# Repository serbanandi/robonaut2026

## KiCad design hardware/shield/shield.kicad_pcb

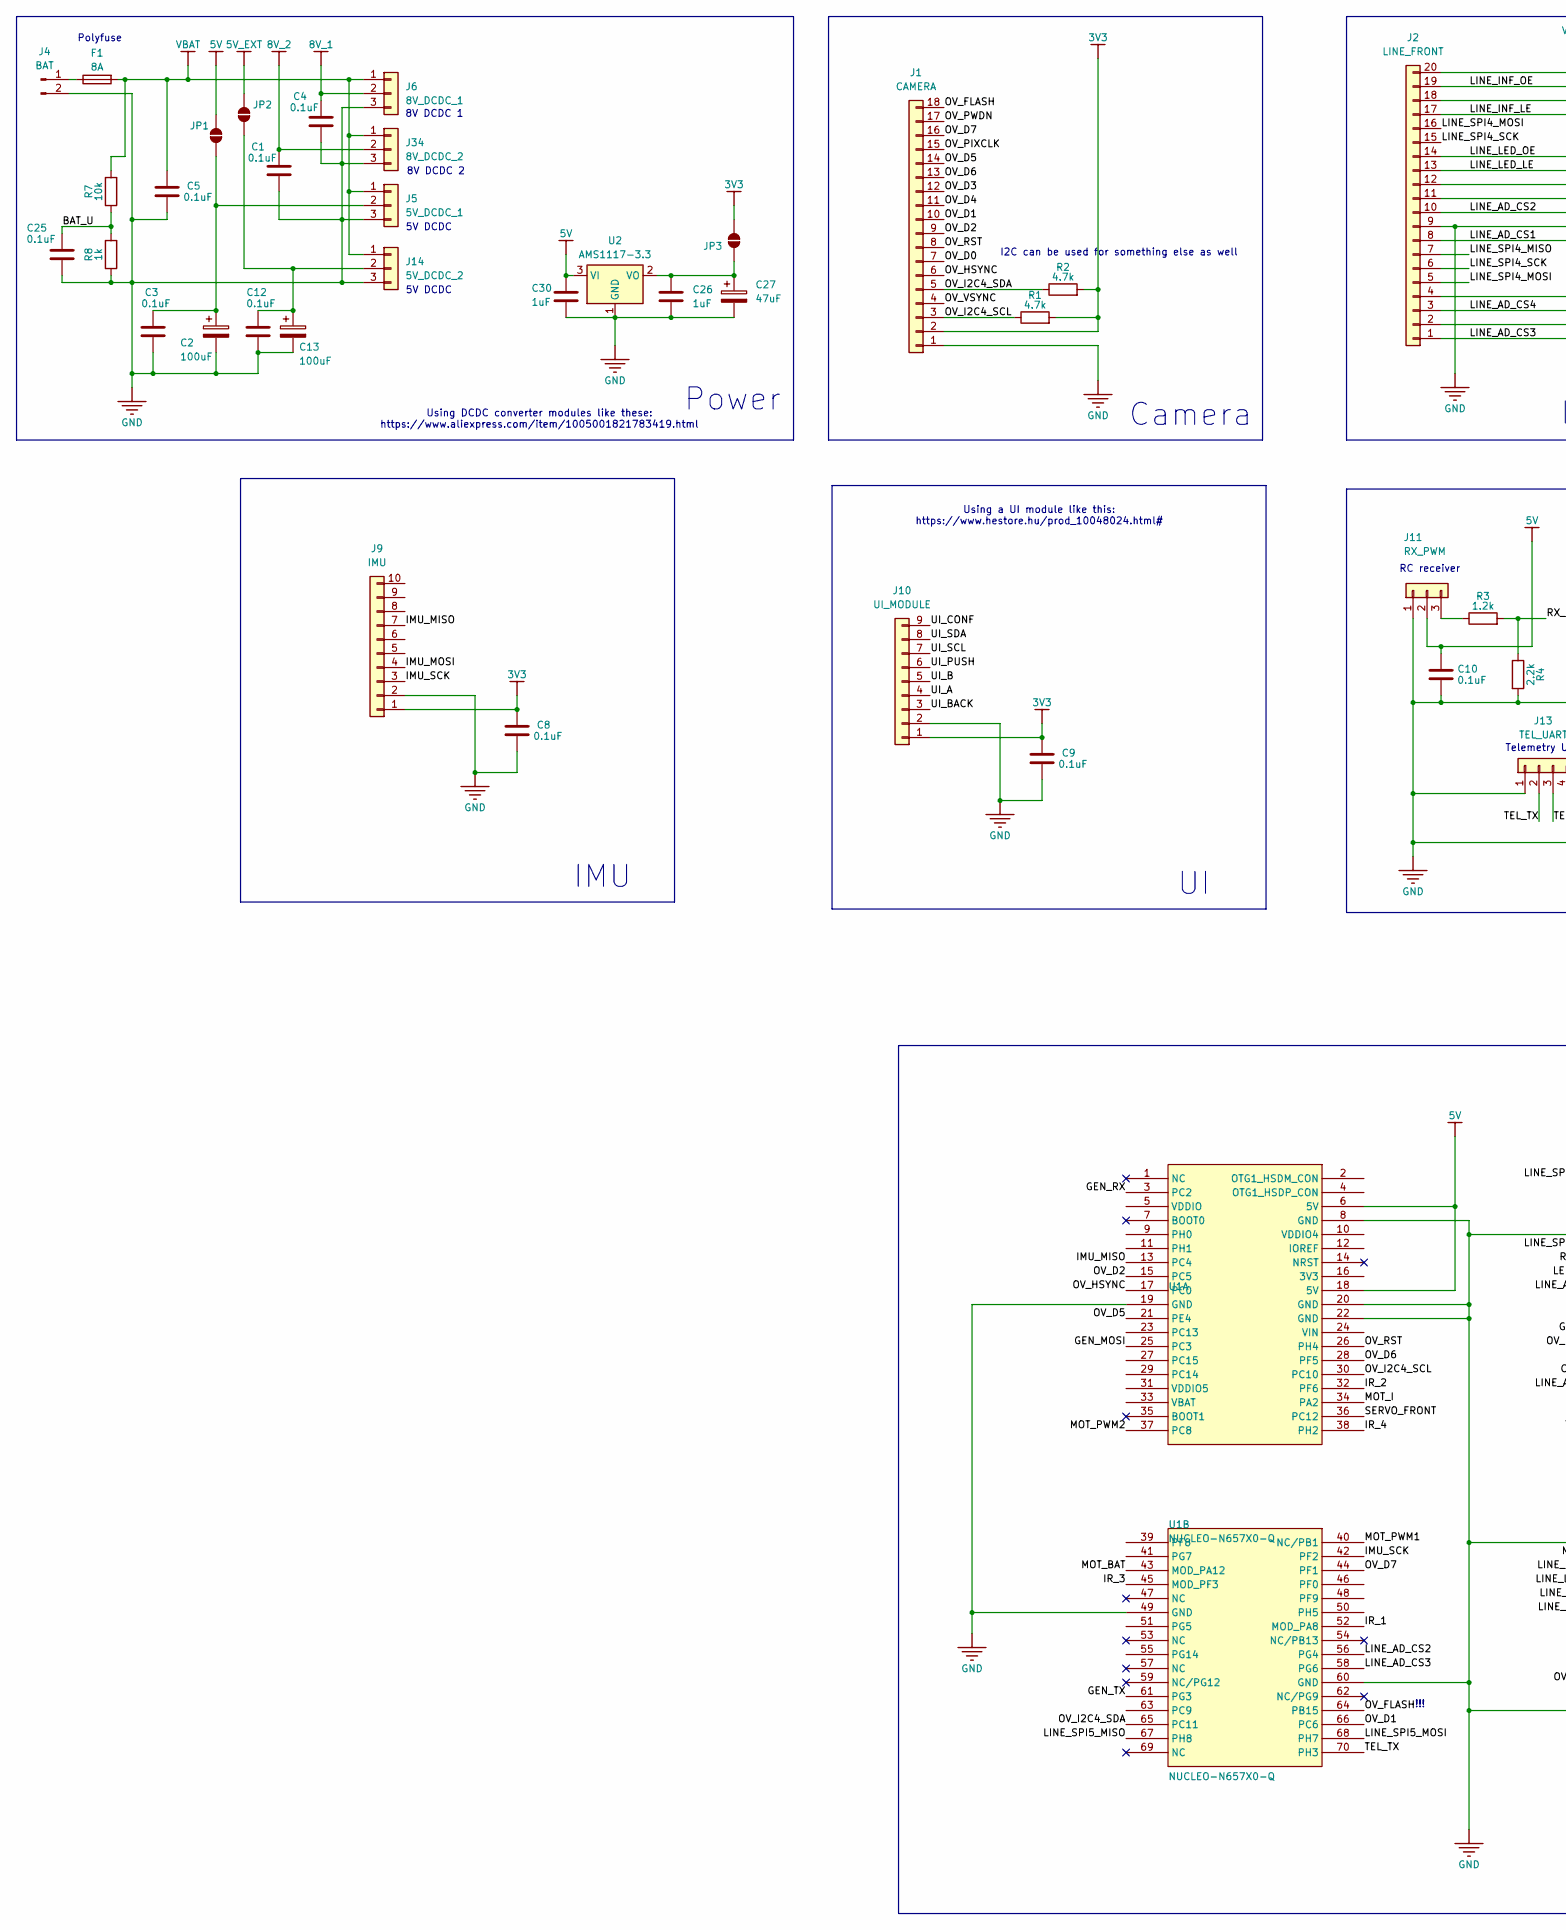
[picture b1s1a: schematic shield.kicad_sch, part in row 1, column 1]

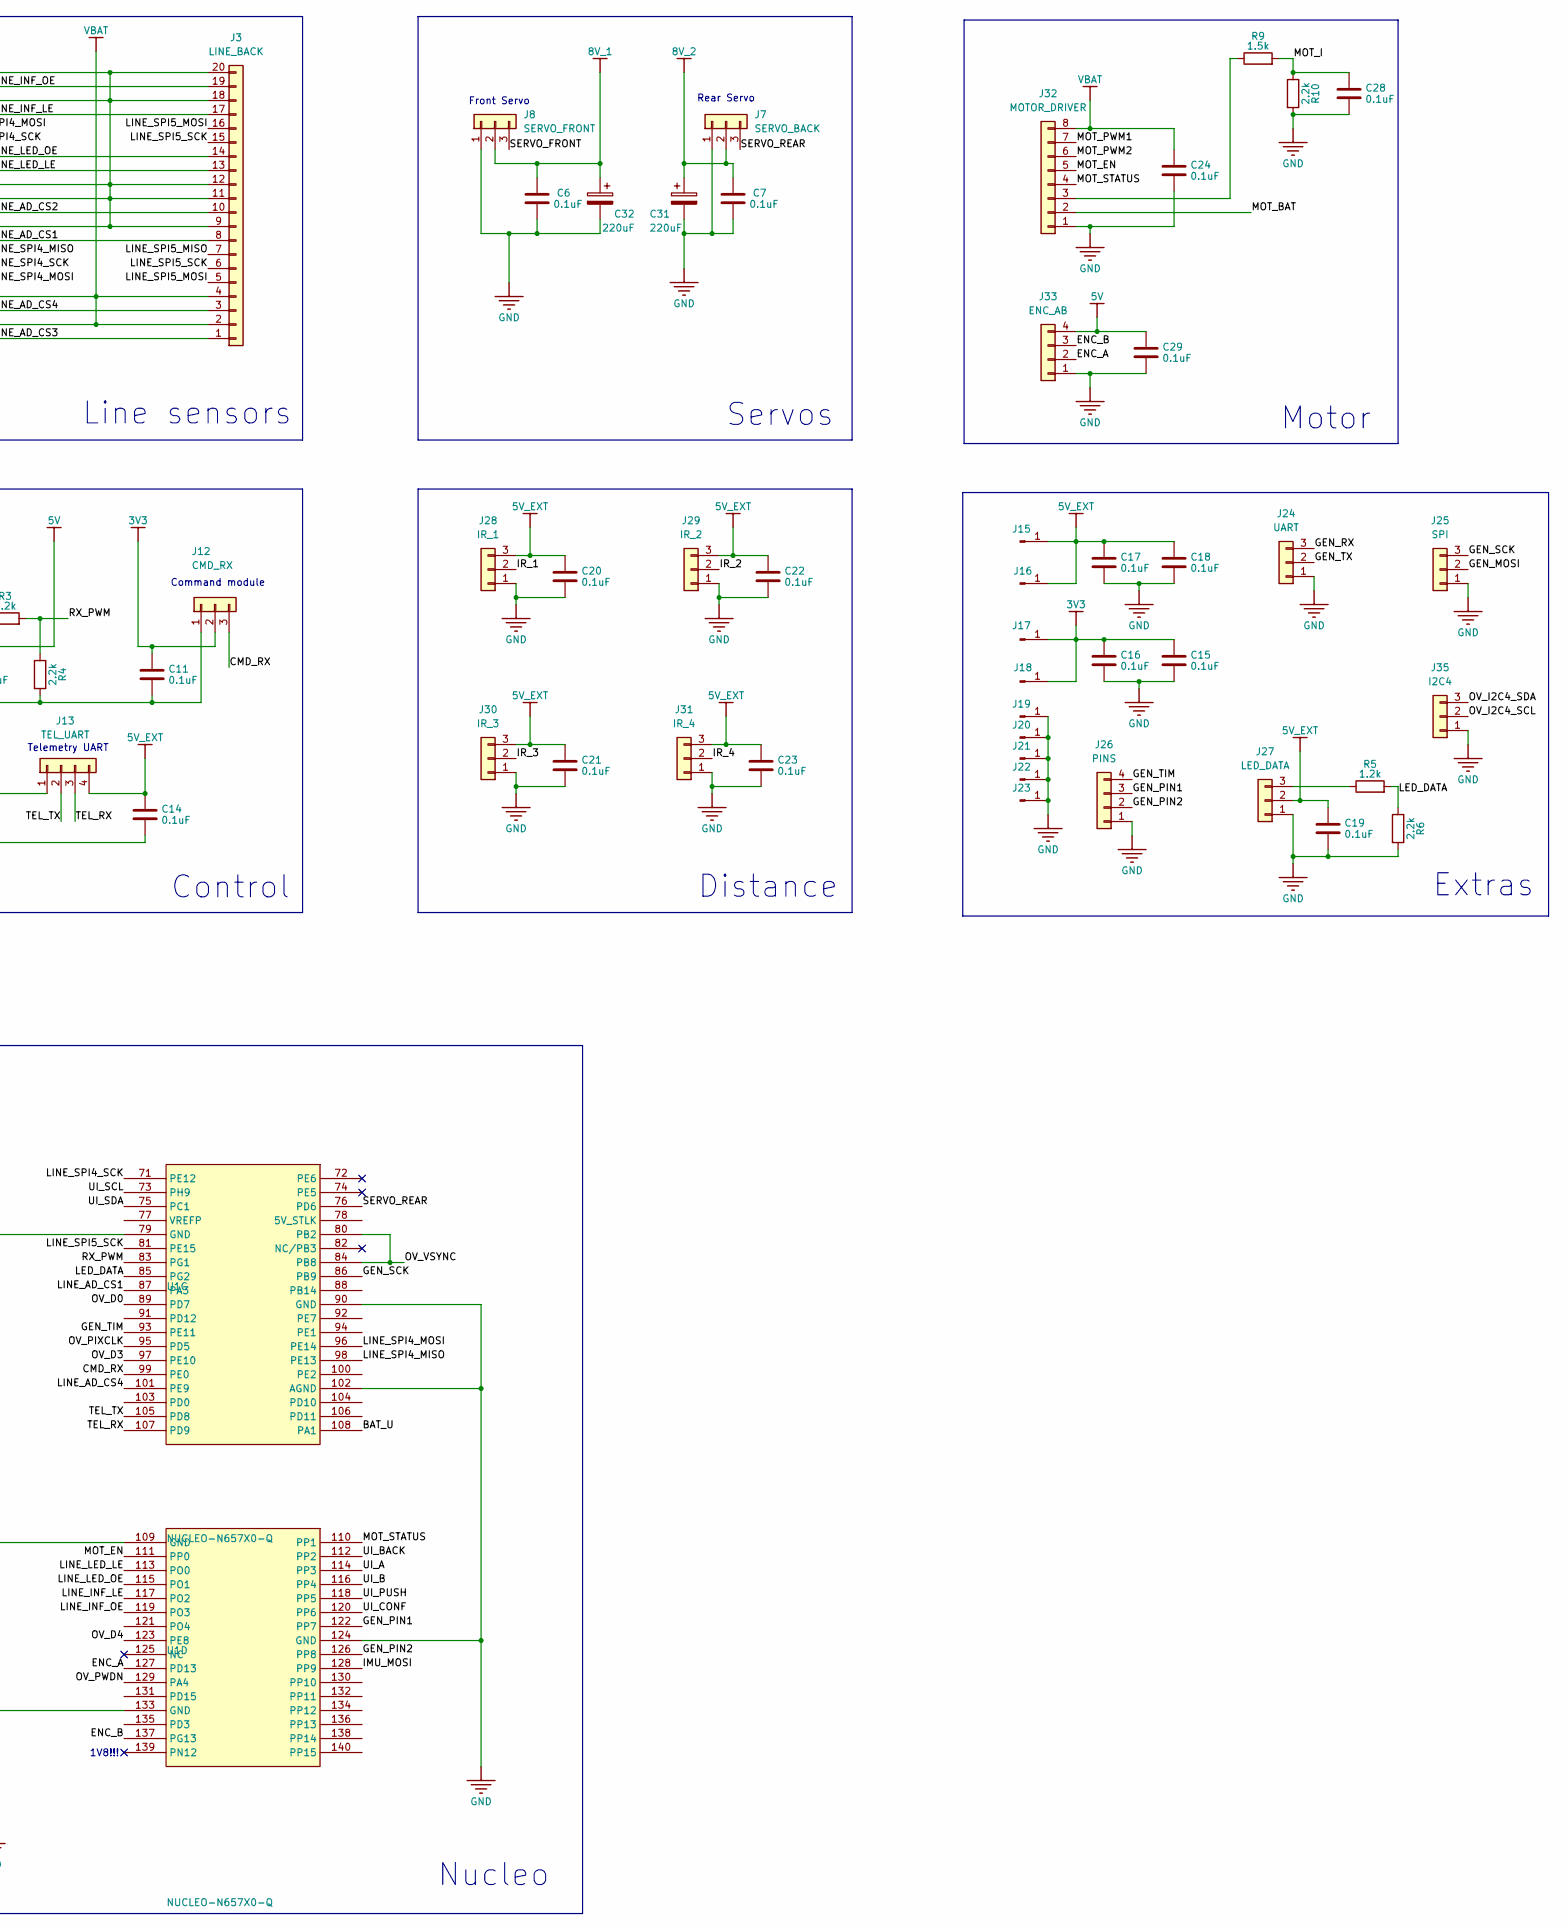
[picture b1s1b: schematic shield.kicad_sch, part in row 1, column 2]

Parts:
C1, C3, C4, C5, C6, C7, C8, C9, C10, C11, C12, C14, C15, C16, C17, C18, C19, C20, C21, C22, C23, C24, C25, C28, C29: 0.1uF; C_0603_1608Metric
C2, C13: 100uF; CP_Elec_5x5.8
C26, C30: 1uF; C_0805_2012Metric
C27: 47uF; CP_Elec_5x5.3
C31, C32: 220uF; CP_Elec_6.3x7.7
F1: 8A; Fuseholder_Blade_Mini_Keystone_3568
J1: CAMERA; PinHeader_2x09_P2.54mm_Horizontal
J2: LINE_FRONT; PinHeader_2x10_P2.54mm_Horizontal
J3: LINE_BACK; PinHeader_2x10_P2.54mm_Horizontal
J4: BAT; TerminalBlock_MaiXu_MX126-5.0-02P_1x02_P5.00mm
J5: 5V_DCDC_1; PinHeader_1x03_P2.54mm_Vertical
J6: 8V_DCDC_1; PinHeader_1x03_P2.54mm_Vertical
J7: SERVO_BACK; PinHeader_1x03_P2.54mm_Horizontal
J8: SERVO_FRONT; PinHeader_1x03_P2.54mm_Horizontal
J9: IMU; PinHeader_1x10_P2.54mm_Vertical
J10: UI_MODULE; JST_SH_SM09B-SRSS-TB_1x09-1MP_P1.00mm_Horizontal
J11: RX_PWM; JST_SH_SM03B-SRSS-TB_1x03-1MP_P1.00mm_Horizontal
J12: CMD_RX; JST_SH_SM03B-SRSS-TB_1x03-1MP_P1.00mm_Horizontal
J13: TEL_UART; JST_SH_SM04B-SRSS-TB_1x04-1MP_P1.00mm_Horizontal
J14: 5V_DCDC_2; PinHeader_1x03_P2.54mm_Vertical
J15: 5V_TP1; Pin_D0.7mm_L6.5mm_W1.8mm_FlatFork
J16: 5V_TP2; Pin_D0.7mm_L6.5mm_W1.8mm_FlatFork
J17: 3V3_TP3; Pin_D0.7mm_L6.5mm_W1.8mm_FlatFork
J18: 3V3_TP4; Pin_D0.7mm_L6.5mm_W1.8mm_FlatFork
J19: GND_TP1; Pin_D0.7mm_L6.5mm_W1.8mm_FlatFork
J20: GND_TP2; Pin_D0.7mm_L6.5mm_W1.8mm_FlatFork
J21: GND_TP3; Pin_D0.7mm_L6.5mm_W1.8mm_FlatFork
J22: GND_TP4; Pin_D0.7mm_L6.5mm_W1.8mm_FlatFork
J23: GND; Pin_D0.7mm_L6.5mm_W1.8mm_FlatFork
J24: UART; PinHeader_1x03_P1.00mm_Vertical
J25: SPI; PinHeader_1x03_P1.00mm_Vertical
J26: PINS; PinHeader_1x04_P1.00mm_Vertical
J27: LED_DATA; JST_SH_SM03B-SRSS-TB_1x03-1MP_P1.00mm_Horizontal
J28: IR_1; JST_SH_SM03B-SRSS-TB_1x03-1MP_P1.00mm_Horizontal
J29: IR_2; JST_SH_SM03B-SRSS-TB_1x03-1MP_P1.00mm_Horizontal
J30: IR_3; JST_SH_SM03B-SRSS-TB_1x03-1MP_P1.00mm_Horizontal
J31: IR_4; JST_SH_SM03B-SRSS-TB_1x03-1MP_P1.00mm_Horizontal
J32: MOTOR_DRIVER; JST_SH_SM08B-SRSS-TB_1x08-1MP_P1.00mm_Horizontal
J33: ENC_AB; JST_SH_SM04B-SRSS-TB_1x04-1MP_P1.00mm_Horizontal
J34: 8V_DCDC_2; PinHeader_1x03_P2.54mm_Vertical
J35: I2C4; PinHeader_1x03_P1.00mm_Vertical
JP1: 5V_1; SolderJumper-2_P1.3mm_Open_TrianglePad1.0x1.5mm
JP2: 5V_2; SolderJumper-2_P1.3mm_Open_TrianglePad1.0x1.5mm
JP3: 3V3; SolderJumper-2_P1.3mm_Open_TrianglePad1.0x1.5mm
R1, R2: 4.7k; R_0603_1608Metric
R3, R5: 1.2k; R_0603_1608Metric
R4, R6, R10: 2.2k; R_0603_1608Metric
R7: 10k; R_0603_1608Metric
R8: 1k; R_0603_1608Metric
R9: 1.5k; R_0603_1608Metric
U1: NUCLEO-N657X0-Q; FP_NUCLEO-144 - N6
U2: AMS1117-3.3; SOT-223-3_TabPin2

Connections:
3V3: C8.1, C9.1, C11.1, C15.1, C16.1, J1.2, J9.1, J10.1, J12.2, J17.1, J18.1, JP3.1 (A), R1.2, R2.2
5V: C10.1, C29.1, C30.1, J11.2, J33.4, JP1.2 (B), U1.6 (5V), U1.18 (5V), U2.3 (VI)
5V_EXT: C14.1, C17.1, C18.1, C19.1, C20.1, C21.1, C22.1, C23.1, J13.4, J15.1, J16.1, J27.2, J28.3, J29.3, J30.3, J31.3, JP2.2 (B)
8V_1: C4.1, C6.1, C32.1, J6.2, J8.2
8V_2: C1.1, C7.1, C31.1, J7.2, J34.2
/BAT_U: C25.1, R7.1, R8.2, U1.108 (PA1)
/CMD_RX: J12.3, U1.99 (PE0)
/ENC_A: J33.2, U1.127 (PD13)
/ENC_B: J33.3, U1.137 (PG13)
/GEN_MOSI: J25.2, U1.25 (PC3)
/GEN_PIN1: J26.3, U1.122 (PP7)
/GEN_PIN2: J26.2, U1.126 (PP8)
/GEN_RX: J24.3, U1.3 (PC2)
/GEN_SCK: J25.3, U1.86 (PB9)
/GEN_TIM: J26.4, U1.93 (PE11)
/GEN_TX: J24.2, U1.61 (PG3)
/IMU_MISO: J9.7, U1.13 (PC4)
/IMU_MOSI: J9.4, U1.128 (PP9)
/IMU_SCK: J9.3, U1.42 (PF2)
/IR_1: J28.2, U1.52 (MOD_PA8)
/IR_2: J29.2, U1.32 (PF6)
/IR_3: J30.2, U1.45 (MOD_PF3)
/IR_4: J31.2, U1.38 (PH2)
/LED_DATA: R5.2, R6.1, U1.85 (PG2)
/LINE_AD_CS1: J2.8, J3.8, U1.87 (PA3)
/LINE_AD_CS2: J2.10, J3.10, U1.56 (PG4)
/LINE_AD_CS3: J2.1, J3.1, U1.58 (PG6)
/LINE_AD_CS4: J2.3, J3.3, U1.101 (PE9)
/LINE_INF_LE: J2.17, J3.17, U1.117 (PO2)
/LINE_INF_OE: J2.19, J3.19, U1.119 (PO3)
/LINE_LED_LE: J2.13, J3.13, U1.113 (PO0)
/LINE_LED_OE: J2.14, J3.14, U1.115 (PO1)
/LINE_SPI4_MISO: J2.7, U1.98 (PE13)
/LINE_SPI4_MOSI: J2.5, J2.16, U1.96 (PE14)
/LINE_SPI4_SCK: J2.6, J2.15, U1.71 (PE12)
/LINE_SPI5_MISO: J3.7, U1.67 (PH8)
/LINE_SPI5_MOSI: J3.5, J3.16, U1.68 (PH7)
/LINE_SPI5_SCK: J3.6, J3.15, U1.81 (PE15)
/MOT_BAT: J32.2, U1.43 (MOD_PA12)
/MOT_EN: J32.5, U1.111 (PP0)
/MOT_I: C28.1, R9.2, R10.1, U1.34 (PA2)
/MOT_PWM1: J32.7, U1.40 (NC/PB1)
/MOT_PWM2: J32.6, U1.37 (PC8)
/MOT_STATUS: J32.4, U1.110 (PP1)
/OV_D0: J1.7, U1.89 (PD7)
/OV_D1: J1.10, U1.66 (PC6)
/OV_D2: J1.9, U1.15 (PC5)
/OV_D3: J1.12, U1.97 (PE10)
/OV_D4: J1.11, U1.123 (PE8)
/OV_D5: J1.14, U1.21 (PE4)
/OV_D6: J1.13, U1.28 (PF5)
/OV_D7: J1.16, U1.44 (PF1)
/OV_FLASH: J1.18, U1.64 (PB15)
/OV_HSYNC: J1.6, U1.17 (PC0)
/OV_I2C4_SCL: J1.3, J35.2, R1.1, U1.30 (PC10)
/OV_I2C4_SDA: J1.5, J35.3, R2.1, U1.65 (PC11)
/OV_PIXCLK: J1.15, U1.95 (PD5)
/OV_PWDN: J1.17, U1.129 (PA4)
/OV_RST: J1.8, U1.26 (PH4)
/OV_VSYNC: J1.4, U1.80 (PB2), U1.84 (PB8)
/RX_PWM: R3.2, R4.1, U1.83 (PG1)
/SERVO_FRONT: J8.3, U1.36 (PC12)
/SERVO_REAR: J7.3, U1.76 (PD6)
/TEL_RX: J13.3, U1.107 (PD9)
/TEL_TX: J13.2, U1.70 (PH3), U1.105 (PD8)
/UI_A: J10.4, U1.114 (PP3)
/UI_B: J10.5, U1.116 (PP4)
/UI_BACK: J10.3, U1.112 (PP2)
/UI_CONF: J10.9, U1.120 (PP6)
/UI_PUSH: J10.6, U1.118 (PP5)
/UI_SCL: J10.7, U1.73 (PH9)
/UI_SDA: J10.8, U1.75 (PC1)
GND: C1.2, C2.2, C3.2, C4.2, C5.2, C6.2, C7.2, C8.2, C9.2, C10.2, C11.2, C12.2, C13.2, C14.2, C15.2, C16.2, C17.2, C18.2, C19.2, C20.2, C21.2, C22.2, C23.2, C24.2, C25.2, C26.2, C27.2, C28.2, C29.2, C30.2, C31.2, C32.2, J1.1, J2.9, J2.11, J2.12, J2.18, J2.20, J3.9, J3.11, J3.12, J3.18, J3.20, J4.2, J5.3, J6.3, J7.1, J8.1, J9.2, J10.2, J11.1, J12.1, J13.1, J14.3, J19.1, J20.1, J21.1, J22.1, J23.1, J24.1, J25.1, J26.1, J27.1, J28.1, J29.1, J30.1, J31.1, J32.1, J33.1, J34.3, J35.1, R4.2, R6.2, R8.1, R10.2, U1.8 (GND), U1.19 (GND), U1.20 (GND), U1.22 (GND), U1.49 (GND), U1.60 (GND), U1.79 (GND), U1.90 (GND), U1.102 (AGND), U1.109 (GND), U1.124 (GND), U1.133 (GND), U2.1 (GND)
unnamed: F1.1, J4.1
unnamed: C2.1, C3.1, J5.2, JP1.1 (A)
unnamed: J11.3, R3.1
unnamed: C12.1, C13.1, J14.2, JP2.1 (A)
unnamed: J27.3, R5.1
unnamed: J32.3, R9.1
unnamed: C26.1, C27.1, JP3.2 (B), U2.2 (VO)
VBAT: C5.1, C24.1, F1.2, J2.2, J2.4, J3.2, J3.4, J5.1, J6.1, J14.1, J32.8, J34.1, R7.2

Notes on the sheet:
Power
Nucleo
Telemetry UART
Line sensors
Camera
Polyfuse
8V DCDC 1
RC receiver
5V DCDC
I2C can be used for something else as well
Motor
8V DCDC 2
!!!
Distance
Command module
IMU
1V8!!!
Front Servo
Using DCDC converter modules like these: https://www.aliexpress.com/item/1005001821783419.html
Using a UI module like this: https://www.hestore.hu/prod_10048024.html#
Rear Servo
Extras
Servos
Control

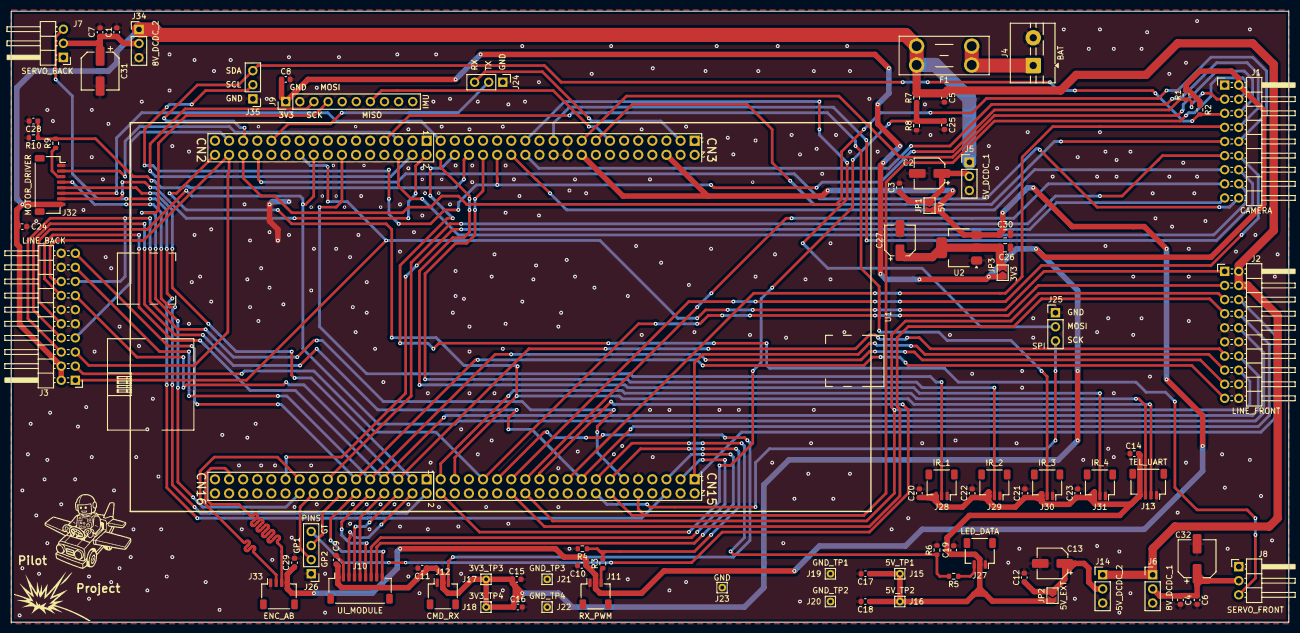
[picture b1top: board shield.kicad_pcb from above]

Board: 2 copper layers, 230.0 x 110.0 mm, 83 parts (0 on the bottom side), 81 nets.

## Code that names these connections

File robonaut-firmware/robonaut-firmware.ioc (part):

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Mcu.Name=STM32N657X0HxQ
Mcu.Package=VFBGA264
Mcu.UserName=STM32N657X0HxQ
PA1.GPIOParameters=GPIO_Label,PinAttribute
PA1.GPIO_Label=BAT_U
PA1.Mode=IN1-Single-Ended
PA1.PinAttribute=Appli
PA1.Signal=ADC2_INP1
PA10.GPIOParameters=GPIO_Label,PinAttribute
PA10.GPIO_Label=IR_2
PA10.Mode=IN11-Single-Ended
PA10.PinAttribute=Appli
PA10.Signal=ADC1_INP11
PA12.GPIOParameters=GPIO_Label,PinAttribute
PA12.GPIO_Label=MOT_U
PA12.Mode=IN13-Single-Ended
PA12.PinAttribute=Appli
PA12.Signal=ADC2_INP13
PA13(JTMS/SWDIO).GPIOParameters=GPIO_Label,PinAttribute
PA13(JTMS/SWDIO).GPIO_Label=SWDIO
PA13(JTMS/SWDIO).Mode=Serial_Wire
PA13(JTMS/SWDIO).PinAttribute=FSBL,Appli
PA13(JTMS/SWDIO).Signal=DEBUG_JTMS-SWDIO
PA14(JTCK/SWCLK).GPIOParameters=GPIO_Label,PinAttribute
PA14(JTCK/SWCLK).GPIO_Label=SWCLK
PA14(JTCK/SWCLK).Mode=Serial_Wire
PA14(JTCK/SWCLK).PinAttribute=FSBL,Appli
PA14(JTCK/SWCLK).Signal=DEBUG_JTCK-SWCLK
PA15(JTDI).GPIOParameters=GPIO_Label,PinAttribute
PA15(JTDI).GPIO_Label=JTDI
PA15(JTDI).PinAttribute=Appli
PA15(JTDI).Signal=DEBUG_JTDI
PA2.GPIOParameters=GPIO_Label,PinAttribute
PA2.GPIO_Label=MOT_I
PA2.Mode=IN14-Single-Ended
PA2.PinAttribute=Appli
PA2.Signal=ADC2_INP14
PA3.ContextOwner=Appli
PA3.GPIOParameters=GPIO_Label,PinAttribute
PA3.GPIO_Label=_AD_CS1 
PA3.PinAttribute=Appli
PA3.Signal=GPIO_Output
PA4.ContextOwner=Appli
PA4.GPIOParameters=GPIO_Label,PinAttribute
PA4.GPIO_Label=OV_PWDN
PA4.PinAttribute=Appli
PA4.Signal=GPXTI4
PA7.GPIOParameters=GPIO_Label,PinAttribute
PA7.GPIO_Label=UCPD_PWR_EN
PA7.PinAttribute=Free
PA7.Signal=GPIO_Output
PA8.GPIOParameters=GPIO_Label,PinAttribute
PA8.GPIO_Label=IR_1
PA8.Mode=IN5-Single-Ended
PA8.PinAttribute=Appli
PA8.Signal=ADC1_INP5
PB0.GPIOParameters=GPIO_Label,PinAttribute
PB0.GPIO_Label=TRACED1
PB0.PinAttribute=Appli
PB0.Signal=DEBUG_TRACED1
PB1.GPIOParameters=GPIO_Label,PinAttribute
PB1.GPIO_Label=GEN_TIM
PB1.PinAttribute=Appli
PB1.Signal=S_TIM3_CH4
PB15.ContextOwner=Appli
PB15.GPIOParameters=GPIO_PuPd,GPIO_Label,GPIO_ModeDefaultOutputPP,PinAttribute
PB15.GPIO_Label=OV_FLASH
PB15.GPIO_ModeDefaultOutputPP=GPIO_MODE_OUTPUT_OD
PB15.GPIO_PuPd=GPIO_NOPULL
PB15.PinAttribute=Appli
PB15.Signal=GPIO_Output
PB2.ContextOwner=Appli
PB2.GPIOParameters=GPIO_Label,PinAttribute
PB2.GPIO_Label=OV_VSYNC
PB2.PinAttribute=Appli
PB2.Signal=GPIO_Input
PB3.GPIOParameters=GPIO_Label,PinAttribute
PB3.GPIO_Label=TRACECLK
PB3.PinAttribute=Appli
PB3.Signal=DEBUG_TRACECLK
PB5(JTDO/TRACESWO).GPIOParameters=GPIO_Label,PinAttribute
PB5(JTDO/TRACESWO).GPIO_Label=SWO
PB5(JTDO/TRACESWO).PinAttribute=Appli
PB5(JTDO/TRACESWO).Signal=DEBUG_JTDO-SWO
PB6.GPIOParameters=GPIO_Label,PinAttribute
PB6.GPIO_Label=TRACED2
PB6.PinAttribute=Appli
PB6.Signal=DEBUG_TRACED2
PB7.GPIOParameters=GPIO_Label,PinAttribute
PB7.GPIO_Label=TRACED3
PB7.PinAttribute=Appli
PB7.Signal=DEBUG_TRACED3
PB8.GPIOParameters=PinAttribute
PB8.Mode=Slave_8_bits_External_Synchro
PB8.PinAttribute=Appli
PB8.Signal=DCMIPP_VSYNC
PB9.GPIOParameters=GPIO_Label,PinAttribute
PB9.GPIO_Label=GEN_SCK
PB9.Mode=TX_Only_Simplex_Unidirect_Master
PB9.PinAttribute=Appli
PB9.Signal=SPI1_SCK
PC0.GPIOParameters=PinAttribute
PC0.Mode=Slave_8_bits_External_Synchro
PC0.PinAttribute=Appli
PC0.Signal=DCMIPP_HSYNC
PC1.GPIOParameters=GPIO_Label,PinAttribute
PC1.GPIO_Label=UI_SDA
PC1.Mode=I2C
PC1.PinAttribute=Appli
PC1.Signal=I2C1_SDA
PC10.GPIOParameters=PinAttribute
PC10.Mode=I2C
PC10.PinAttribute=Appli
PC10.Signal=I2C4_SCL
PC11.GPIOParameters=PinAttribute
PC11.Mode=I2C
PC11.PinAttribute=Appli
PC11.Signal=I2C4_SDA
PC12.GPIOParameters=GPIO_Label,PinAttribute
PC12.GPIO_Label=SERVO_FRONT
PC12.PinAttribute=Appli
PC12.Signal=S_TIM15_CH1
PC13.Signal=GPIO_Input
PC2.GPIOParameters=GPIO_Label,PinAttribute
PC2.GPIO_Label=GEN_RX
PC2.Mode=Asynchronous
PC2.PinAttribute=Appli
PC2.Signal=USART2_RX
PC3.GPIOParameters=GPIO_Label,PinAttribute
PC3.GPIO_Label=GEN_MOSI
PC3.Mode=TX_Only_Simplex_Unidirect_Master
PC3.PinAttribute=Appli
PC3.Signal=SPI1_MOSI
PC4.GPIOParameters=GPIO_Label,PinAttribute
PC4.GPIO_Label=IMU_MISO
PC4.Mode=Full_Duplex_Master
PC4.PinAttribute=Appli
PC4.Signal=SPI2_MISO
PC5.GPIOParameters=PinAttribute
PC5.Mode=Slave_8_bits_External_Synchro
PC5.PinAttribute=Appli
PC5.Signal=DCMIPP_D2
PC6.GPIOParameters=PinAttribute
PC6.Mode=Slave_8_bits_External_Synchro
PC6.PinAttribute=Appli
PC6.Signal=DCMIPP_D1
PC8.ContextOwner=Appli
PC8.GPIOParameters=GPIO_Label,PinAttribute
PC8.GPIO_Label=_AD_CS4
PC8.PinAttribute=Appli
PC8.Signal=GPIO_Output
PD10.ContextOwner=Appli
PD10.GPIOParameters=GPIO_Label,PinAttribute
PD10.GPIO_Label=PWR_EN
PD10.PinAttribute=Appli
PD10.Signal=GPIO_Output
PD13.GPIOParameters=GPIO_Label,PinAttribute
PD13.GPIO_Label=ENC_A
PD13.PinAttribute=Appli
PD13.Signal=S_TIM4_CH2
PD2.GPIOParameters=GPIO_Label,PinAttribute
PD2.GPIO_Label=UCPD1_INT
PD2.PinAttribute=Free
PD2.Signal=GPIO_Input
PD5.GPIOParameters=PinAttribute
PD5.Mode=Slave_8_bits_External_Synchro
PD5.PinAttribute=Appli
PD5.Signal=DCMIPP_PIXCLK
PD6.GPIOParameters=GPIO_Label,PinAttribute
PD6.GPIO_Label=SERVO_REAR
PD6.PinAttribute=Appli
PD6.Signal=S_TIM15_CH2
PD7.GPIOParameters=PinAttribute
PD7.Mode=Slave_8_bits_External_Synchro
PD7.PinAttribute=Appli
PD7.Signal=DCMIPP_D0
PD8.GPIOParameters=GPIO_Label,PinAttribute
PD8.GPIO_Label=TEL_TX
PD8.Mode=Asynchronous
PD8.PinAttribute=Appli
PD8.Signal=USART3_TX
PD9.GPIOParameters=GPIO_Label,PinAttribute
PD9.GPIO_Label=TEL_RX
PD9.Mode=Asynchronous
PD9.PinAttribute=Appli
PD9.Signal=USART3_RX
PE0.GPIOParameters=GPIO_Label,PinAttribute
PE0.GPIO_Label=CMD_RX
PE0.Mode=Asynchronous
PE0.PinAttribute=Appli
PE0.Signal=UART8_RX
PE1.GPIOParameters=PinAttribute
PE1.Mode=Asynchronous
PE1.PinAttribute=Appli
PE1.Signal=UART8_TX
PE10.GPIOParameters=PinAttribute
PE10.Mode=Slave_8_bits_External_Synchro
PE10.PinAttribute=Appli
PE10.Signal=DCMIPP_D3
PE11.GPIOParameters=GPIO_Label,PinAttribute
PE11.GPIO_Label=MOT_PWM1
PE11.PinAttribute=Appli
PE11.Signal=S_TIM1_CH2
PE12.GPIOParameters=PinAttribute
PE12.Mode=Full_Duplex_Master
PE12.PinAttribute=Appli
PE12.Signal=SPI4_SCK
PE13.GPIOParameters=PinAttribute
PE13.Mode=Full_Duplex_Master
PE13.PinAttribute=Appli
PE13.Signal=SPI4_MISO
PE14.GPIOParameters=PinAttribute
PE14.Mode=Full_Duplex_Master
PE14.PinAttribute=Appli
PE14.Signal=SPI4_MOSI
PE15.GPIOParameters=PinAttribute
PE15.Mode=Full_Duplex_Master
PE15.PinAttribute=Appli
PE15.Signal=SPI5_SCK
PE3.GPIOParameters=GPIO_Label,PinAttribute
PE3.GPIO_Label=TRACED0
PE3.PinAttribute=Appli
PE3.Signal=DEBUG_TRACED0
PE4.GPIOParameters=PinAttribute
PE4.Mode=Slave_8_bits_External_Synchro
PE4.PinAttribute=Appli
PE4.Signal=DCMIPP_D5
PE5.Mode=I2C
PE5.Signal=I2C1_SCL
PE8.GPIOParameters=PinAttribute
PE8.Mode=Slave_8_bits_External_Synchro
PE8.PinAttribute=Appli
PE8.Signal=DCMIPP_D4
PE9.GPIOParameters=GPIO_Label,PinAttribute
PE9.GPIO_Label=MOT_PWM2
PE9.PinAttribute=Appli
PE9.Signal=S_TIM1_CH1
PF1.GPIOParameters=PinAttribute
PF1.Mode=Slave_8_bits_External_Synchro
PF1.PinAttribute=Appli
PF1.Signal=DCMIPP_D7
PF2.GPIOParameters=GPIO_Label,PinAttribute
PF2.GPIO_Label=IMU_SCK
PF2.Mode=Full_Duplex_Master
PF2.PinAttribute=Appli
PF2.Signal=SPI2_SCK
PF3.GPIOParameters=GPIO_Label,PinAttribute
PF3.GPIO_Label=IR_3
PF3.Mode=IN16-Single-Ended
PF3.PinAttribute=Appli
PF3.Signal=ADC1_INP16
PF5.GPIOParameters=PinAttribute
PF5.Mode=Slave_8_bits_External_Synchro
PF5.PinAttribute=Appli
PF5.Signal=DCMIPP_D6
PG0.Signal=GPIO_Output
PG1.GPIOParameters=GPIO_Label,PinAttribute
PG1.GPIO_Label=RX_PWM
PG1.PinAttribute=Appli
PG1.Signal=S_TIM13_CH1
PG10.Signal=GPIO_Output
PG13.GPIOParameters=GPIO_Label,PinAttribute
PG13.GPIO_Label=ENC_B
PG13.PinAttribute=Appli
PG13.Signal=S_TIM4_CH1
PG15.GPIOParameters=GPIO_Label,PinAttribute
PG15.GPIO_Label=IR_4
PG15.Mode=IN7-Single-Ended
PG15.PinAttribute=Appli
PG15.Signal=ADC1_INP7
PG2.GPIOParameters=PinAttribute
PG2.Mode=Output Compare1 CH1N
PG2.PinAttribute=Appli
PG2.Signal=TIM17_CH1N
PG3.GPIOParameters=GPIO_Label,PinAttribute
PG3.GPIO_Label=GEN_TX
PG3.Mode=Asynchronous
PG3.PinAttribute=Appli
PG3.Signal=USART2_TX
PG4.ContextOwner=Appli
PG4.GPIOParameters=GPIO_Label,PinAttribute
PG4.GPIO_Label=_AD_CS2 
PG4.PinAttribute=Appli
PG4.Signal=GPIO_Output
PG6.ContextOwner=Appli
PG6.GPIOParameters=GPIO_Label,PinAttribute
PG6.GPIO_Label=_AD_CS3 
PG6.PinAttribute=Appli
PG6.Signal=GPIO_Output
PG7.ContextOwner=Appli
PG7.GPIOParameters=GPIO_Label,PinAttribute
PG7.GPIO_Label=IMU_CS
PG7.PinAttribute=Appli
PG7.Signal=GPIO_Output
PG8.Signal=GPIO_Output
PH0-OSC_IN(PH0).GPIOParameters=PinAttribute
PH0-OSC_IN(PH0).Mode=HSE-External-Oscillator
PH0-OSC_IN(PH0).PinAttribute=Free
PH0-OSC_IN(PH0).Signal=RCC_OSC_IN
PH1-OSC_OUT(PH1).GPIOParameters=PinAttribute
PH1-OSC_OUT(PH1).Mode=HSE-External-Oscillator
PH1-OSC_OUT(PH1).PinAttribute=Free
PH1-OSC_OUT(PH1).Signal=RCC_OSC_OUT
PH4.ContextOwner=Appli
PH4.GPIOParameters=GPIO_Label,PinAttribute
PH4.GPIO_Label=OV_RST
PH4.PinAttribute=Appli
PH4.Signal=GPIO_Output
PH7.GPIOParameters=PinAttribute
PH7.Mode=Full_Duplex_Master
PH7.PinAttribute=Appli
PH7.Signal=SPI5_MOSI
PH8.GPIOParameters=PinAttribute
PH8.Mode=Full_Duplex_Master

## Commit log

2025-09-22 hw architecture
2025-09-27 fw skeleton
2025-09-27 schematic design started
2025-09-27 post build script fix
2025-10-04 first schematic version and .ioc pin config
2025-10-12 minor sch fixes and footprint assignment
2025-10-12 larger pin headers
2025-10-16 Approx layout done
2025-10-18 PCB v1 done
2025-10-20 Fixed DRCs, added labels to silkscreen
2025-11-16 Project restructuring, UI and test code
2025-11-17 servo impl and motor pwm pin changes
2025-11-18 Line following control logic added
2025-11-18 Added define for 1 line sensor
2025-11-18 motor driver impl
2025-11-18 controller tuning with UI module
2025-11-18 line detection done
2025-11-18 a shitty shit
2025-11-18 value fixes
2025-11-18 added logic for controller tuning
2025-11-19 qualifying params
2025-11-19 q1 win
2025-12-12 add rpi telemetry
2025-12-12 implement initial telemetry and uart version
2025-12-12 fix telemetry issues and refactor code
2025-12-12 convert uart operations to use dma
2025-12-13 start drive module impl
2025-12-14 add imu cs pin config and fix ui module init freeze
2025-12-14 implement basic drive module
2025-12-14 add tim18 for imu readouts
2025-12-14 IMU driver and init
2025-12-14 implement q1 task again
2025-12-14 save pre q2 task mod state
2025-12-15 implement basic line split navigation
2025-12-15 q2 solution v1 - junctions unstable
2025-12-15 q2 solution v1.1 - junctions still unstable
2025-12-15 start robust navigation impl
2026-01-16 implement vscode development support
2026-01-16 format relevant sources using clang
2026-01-17 linux compatible build script
2026-01-27 RC trigger control
2026-01-29 RC util
2026-01-29 implement analog module and refactor LineSensor
2026-01-29 modify cubemx config for rc rx driver
2026-01-29 RC fix mert buzis normálisan ledokumentálni az időzítést
2026-01-29 RC added to sys init
2026-01-29 RC added to sys main
2026-01-29 make test code prerier and fix minor things
2026-01-29 change cubemx config for camera integration
2026-01-30 distance sensor conversion
2026-01-30 add dma2d to cubemx config
2026-01-30 add middlewares library to project
2026-01-31 integrate initial camera ai demo
2026-01-31 eliminate diffs compared to example code
2026-01-31 fix camera pwdn and flash pin config
2026-01-31 add --specs=nosys.specs linker flag
2026-01-31 new robust navigation
2026-01-31 fsbl shell script
